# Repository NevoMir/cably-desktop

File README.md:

# Cably Desktop

**Cably Desktop** is the desktop app for [cably.dev](https://cably.dev): a fork of
[KiCad](https://www.kicad.org) that opens the projects you generate on Cably in KiCad's
real editors and syncs your edits back. It is **based on KiCad**; it is not KiCad and is not
affiliated with or endorsed by the KiCad project. "KiCad" is a registered trademark of
LF Projects, LLC.

- Licence: GNU General Public License v3.0 or later, like KiCad (see `LICENSE.README`).
  This repository is the complete corresponding source for every Cably Desktop build.
- What Cably changed: everything under `cably/`, plus the edits recorded in `CHANGES.md`
  (the GPLv3 §5(a) record). Upstream KiCad's copyright and notices are unchanged.
- Build on macOS: `cably/toolchain/README.md`. Tests: `cably/tests/`.
- Cably's cloud services are separate, closed-source products; this app talks to them
  over HTTPS with a public key and nothing more.

The original KiCad README follows.

---

# KiCad README

For specific documentation about [building KiCad](https://dev-docs.kicad.org/en/build/), policies
and guidelines, and source code documentation see the
[Developer Documentation](https://dev-docs.kicad.org) website.

You may also take a look into the [Wiki](https://gitlab.com/kicad/code/kicad/-/wikis/home),
the [contribution guide](https://dev-docs.kicad.org/en/contribute/).

For general information about KiCad and information about contributing to the documentation and
libraries, see our [Website](https://kicad.org/) and our [Forum](https://forum.kicad.info/).

## Build state

KiCad uses a host of CI resources.

GitLab CI pipeline status can be viewed for Linux and Windows builds of the latest commits.

## Release status

## Files
* [AUTHORS.txt](AUTHORS.txt) - The authors, contributors, document writers and translators list
* [CMakeLists.txt](CMakeLists.txt) - Main CMAKE build tool script
* [copyright.h](copyright.h) - A very short copy of the GNU General Public License to be included in new source files
* [Doxyfile](Doxyfile) - Doxygen config file for KiCad
* [INSTALL.txt](INSTALL.txt) - The release (binary) installation instructions
* [uncrustify.cfg](uncrustify.cfg) - Uncrustify config file for uncrustify sources formatting tool
* [_clang-format](_clang-format) - clang config file for clang-format sources formatting tool

## Subdirectories

* [3d-viewer](3d-viewer)         - Sourcecode of the 3D viewer
* [bitmap2component](bitmap2component)  - Sourcecode of the bitmap to PCB artwork converter
* [cmake](cmake)      - Modules for the CMAKE build tool
* [common](common)            - Sourcecode of the common library
* [cvpcb](cvpcb)             - Sourcecode of the CvPCB tool
* [demos](demos)             - Some demo examples
* [doxygen](doxygen)     - Configuration for generating pretty doxygen manual of the codebase
* [eeschema](eeschema)          - Sourcecode of the schematic editor
* [gerbview](gerbview)          - Sourcecode of the gerber viewer
* [include](include)           - Interfaces to the common library
* [kicad](kicad)             - Sourcecode of the project manager
* [libs](libs)           - Sourcecode of KiCad utilities (geometry and others)
* [pagelayout_editor](pagelayout_editor) - Sourcecode of the pagelayout editor
* [patches](patches)           - Collection of patches for external dependencies
* [pcbnew](pcbnew)           - Sourcecode of the printed circuit board editor
* [plugins](plugins)           - Sourcecode for the 3D viewer plugins
* [qa](qa)                - Unit testing framework for KiCad
* [resources](resources)         - Packaging resources such as bitmaps and operating system specific files
    - [bitmaps_png](resources/bitmaps_png)       - Menu and program icons
    - [project_template](resources/project_template)          - Project template
* [scripting](scripting)         - Python integration for KiCad
* [thirdparty](thirdparty)           - Sourcecode of external libraries used in KiCad but not written by the KiCad team
* [tools](tools)             - Helpers for developing, testing and building
* [translation](translation) - Translation data files (managed through [Weblate](https://hosted.weblate.org/projects/kicad/master-source/) for most languages)
* [utils](utils)             - Small utils for KiCad, e.g. IDF, STEP, and OGL tools and converters

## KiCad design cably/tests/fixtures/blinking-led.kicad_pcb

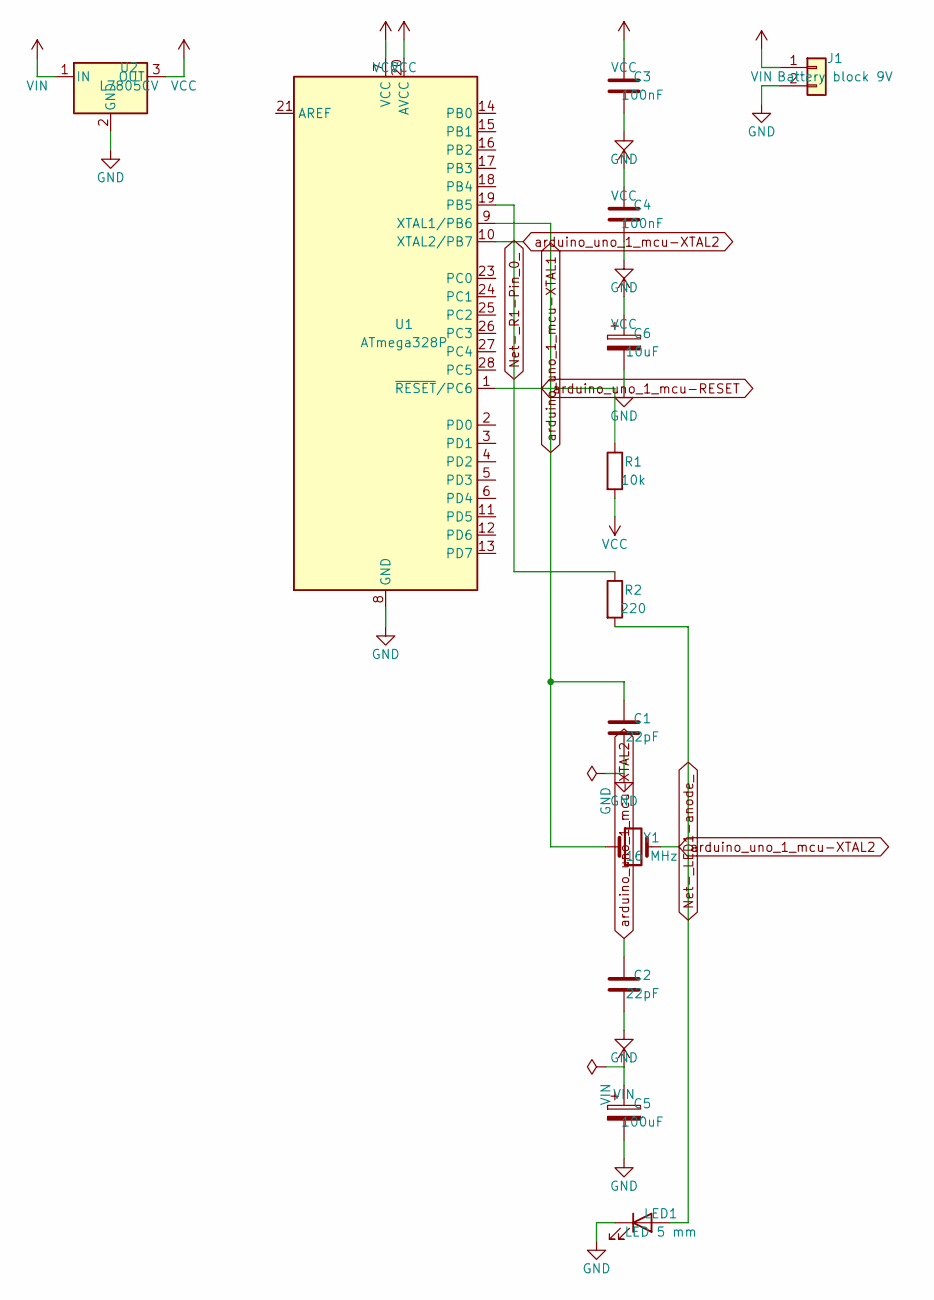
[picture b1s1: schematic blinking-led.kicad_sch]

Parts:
C1, C2: 22pF
C3, C4: 100nF
C5: 100uF
C6: 10uF
J1: Battery block 9V
LED1: LED 5 mm
R1: 10k
R2: 220
U1: ATmega328P
U2: L7805CV
Y1: 16 MHz

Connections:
GND: C1.2, C2.2, C3.2, C4.2, C5.2, C6.2, J1.2, LED1.1 (K), U1.8 (GND), U1.22 (GND), U2.2 (GND)
unnamed: LED1.2 (A), R2.2
unnamed: R2.1, U1.19 (PB5)
VCC: C3.1, C4.1, C6.1, R1.2, U1.7 (VCC), U1.20 (AVCC), U2.3 (OUT)
VIN: C5.1, J1.1, U2.1 (IN)
arduino_uno_1_mcu-RESET: R1.1, U1.1 (~RESET/PC6)
arduino_uno_1_mcu-XTAL1: C1.1, U1.9 (XTAL1/PB6), Y1.1
arduino_uno_1_mcu-XTAL2: C2.1, U1.10 (XTAL2/PB7), Y1.2

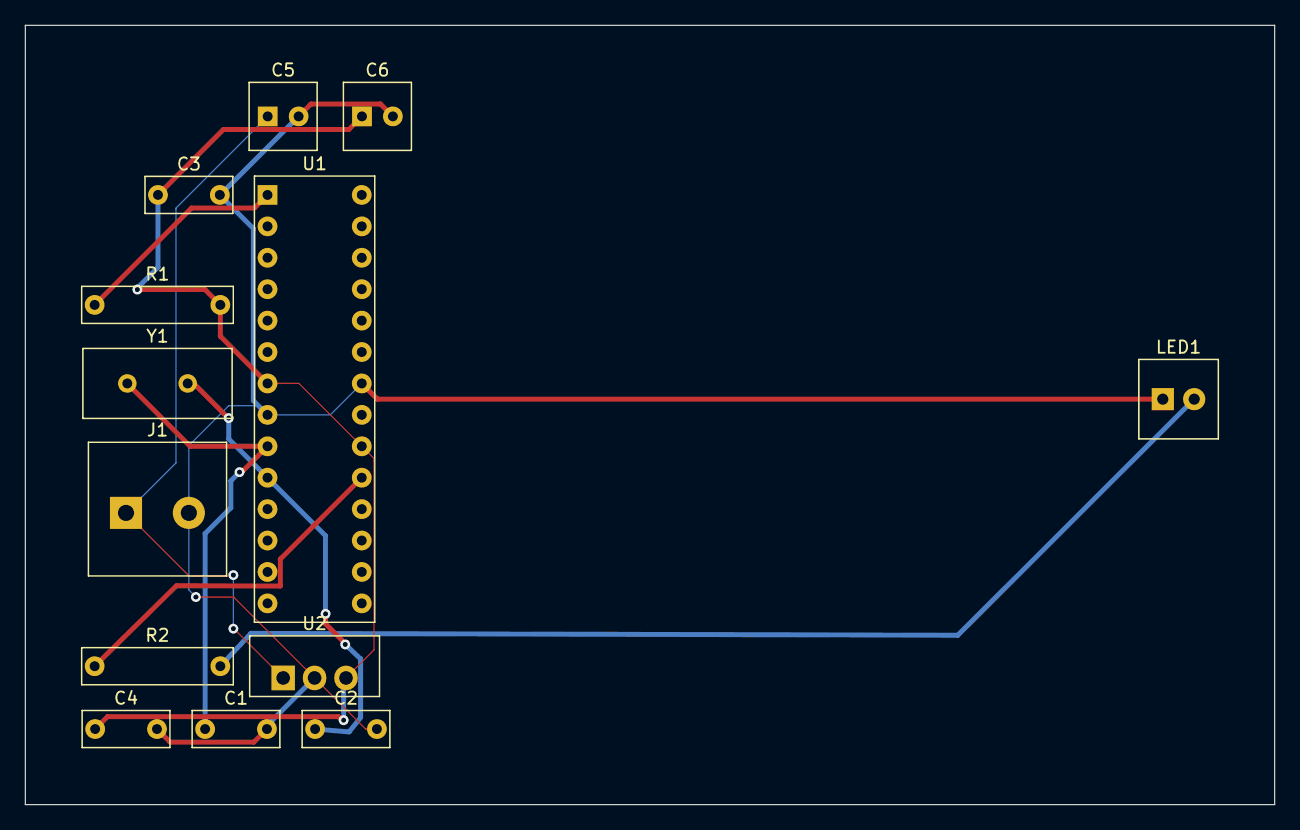
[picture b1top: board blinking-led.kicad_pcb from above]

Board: 2 copper layers, 101.0 x 63.0 mm, 13 parts (0 on the bottom side), 8 nets.
